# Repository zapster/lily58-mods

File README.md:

# Lily58 Mods
Modifications and enhancements for the Lily58 keyboard.

This is currently work in progress.

## Firmware
QMK with the `zapster` keymap for the Lily58 keyboard: https://github.com/zapster/qmk_firmware

## USB C Interconnect

Replace the TRRS connection with an USB C receptacle to avoid short curcuits.
The idea is to create a PCB that can be soldered to the TRRS jacks footprint.
Since the USB C is non-standard and might be confused with the USB jacks on the MCU,
the interconnect will likely use a magnetic USB C cable.

Go to [Lily58_Pro_USB_C_Reset_Ext](./Lily58_Pro_USB_C_Reset_Ext/)

### Part Evaluation:
* USB C recaptacle: USB4110-GF-A
* Magnetic USB C cable: https://www.amazon.de/gp/product/B0B76D7L5Q/ref=ppx_yo_dt_b_asin_title_o01_s00?ie=UTF8&th=1
  * need to check number of wires and connectivity

## Palm Rest

Add a palm rest and potentially 3d print a case that supports it, also wrt. tenting.

### Parts

* first try: [Kensington K52802WW](https://www.kensington.com/p/products/ergonomic-desk-accessories/ergosoft-wrist-rest/kensington-ergosoft-wrist-rest-for-standard-mouse/)
  * not comfortable
* currently testing: non-name "Powcan Memory Foam" https://www.amazon.de/gp/product/B07JGDDCJM/ref=ppx_yo_dt_b_asin_title_o00_s00?ie=UTF8&psc=1
  * until now, rather nice

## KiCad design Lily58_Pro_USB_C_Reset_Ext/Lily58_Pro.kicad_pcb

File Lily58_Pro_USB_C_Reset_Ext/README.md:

# Lily58 USB C Interconnect and Side-Reset Extension

Small extension board that adds an USB C jack for connecting the two keyboard sides
and a side-facing reset button.
The extension board is soldered onto the TRRS jack and reset button pads of the original Lily58 Pro PCB.

Similar to the main Lily58 board, the extension PCB is reversible,
so the same board can be used for the right and left side of the keyboard.

## Revision ExtUR0

The ExtUR0 revision of the PCB as been sent to the fab on 2022-11-15.

### Rendering

#### Front/Right Side

#### Back/Left Side

### Holes

| Component | Hole | Pad |
| ----------| ---- | --- |
| TRRS jack | 0.5mm x 1.6mm |1.2mm x 2.1mm|
| R1, R2, P1, P2 | 32mil (0.8128mm) | 55mil (1.3970mm) |
| Reset button | 1.3mm | 2.5mm |

### Bill of Material

For both keyboard sides.

| Qty | Part          | Description       | Comment |
| --- | ------------- | ----------------  | --- |
|   2 | TL3330AF130QG | Side-reset button | |
|   2 | USB4110-GF-A  | USB C receptacle  | |
|   8 | 3121-2-00-15-00-00-08-0 | Mill Max pin | TRRS |
|   4 | 3136-1-00-15-00-00-08-0 | Mill Max pin | Reset Button |

### Known Issues

* The part names and the board name silk screens are face the other direction. Since the parts are inherited from the Lily58 PCB, the board name should be flipped.
* All holes that connect to the Lily58 Pro PCB should probably use the same size for simplicity.

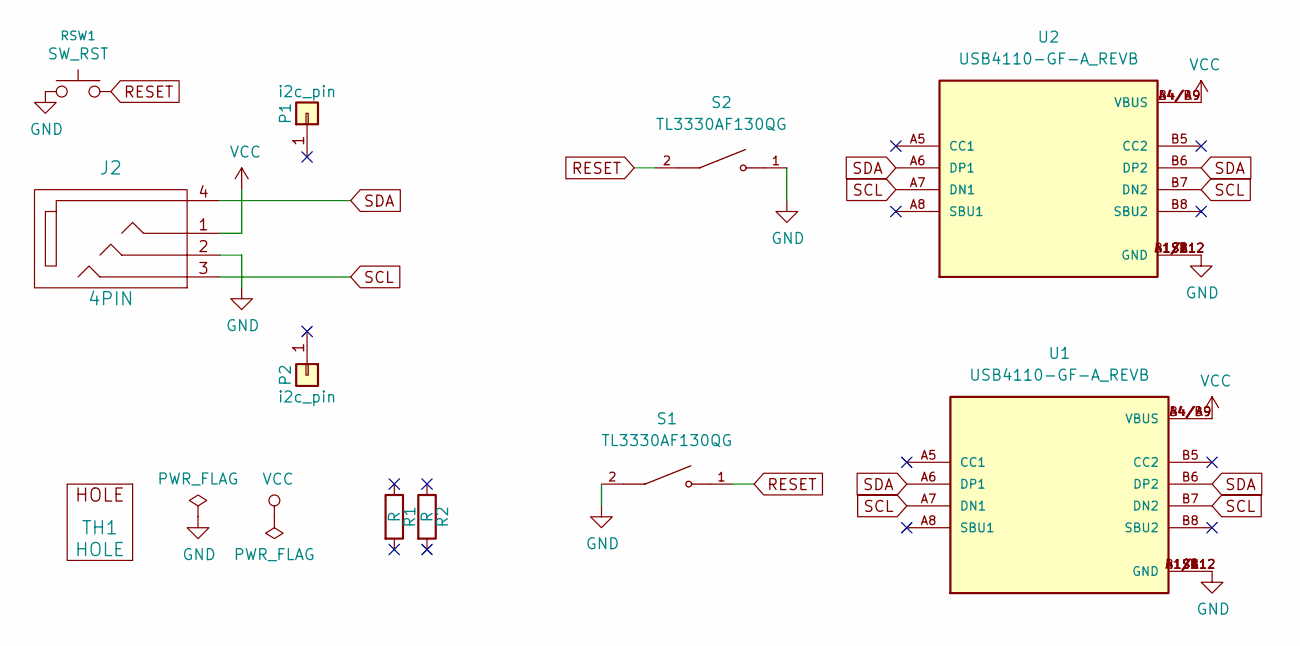
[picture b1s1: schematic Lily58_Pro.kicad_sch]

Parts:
J2: 4PIN; MJ-4PP-9
P1, P2: i2c_pin; 1pin_conn
R1, R2: R; RESISTOR_mini
RSW1: SW_RST; TACT_SWITCH_TVBP06
S1, S2: TL3330AF130QG; SW_TL3330AF130QG; PARTREV B
TH1: HOLE; M2_HOLE_PCB
U1, U2: USB4110-GF-A_REVB; GCT_USB4110-GF-A_REVB; PARTREV B

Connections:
GND: J2.2, RSW1.1, S1.2, S2.1, U1.A1/B12 (GND), U1.B1/A12 (GND), U1.S1 (GND), U1.S2 (GND), U1.S3 (GND), U1.S4 (GND), U2.A1/B12 (GND), U2.B1/A12 (GND), U2.S1 (GND), U2.S2 (GND), U2.S3 (GND), U2.S4 (GND)
RESET: RSW1.2, S1.1, S2.2
SCL: J2.3, U1.A7 (DN1), U1.B7 (DN2), U2.A7 (DN1), U2.B7 (DN2)
SDA: J2.4, U1.A6 (DP1), U1.B6 (DP2), U2.A6 (DP1), U2.B6 (DP2)
VCC: J2.1, U1.A4/B9 (VBUS), U1.B4/A9 (VBUS), U2.A4/B9 (VBUS), U2.B4/A9 (VBUS)

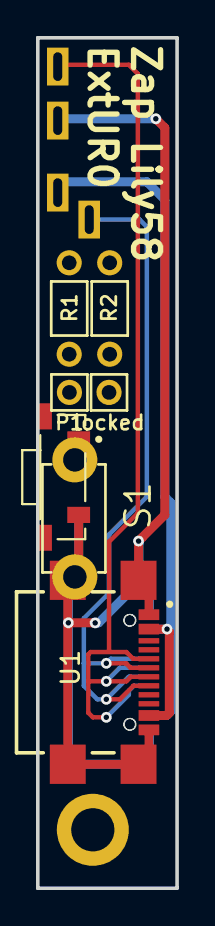
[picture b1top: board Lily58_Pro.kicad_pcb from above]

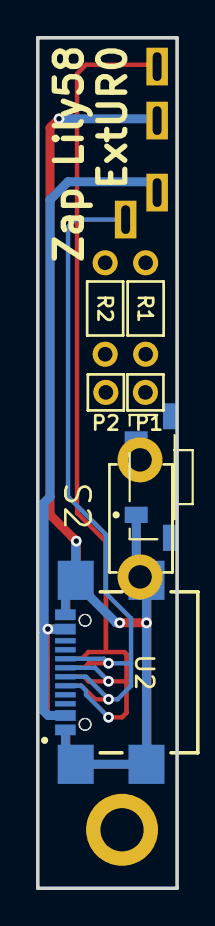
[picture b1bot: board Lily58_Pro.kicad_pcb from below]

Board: 2 copper layers, 7.7 x 47.2 mm, 11 parts (2 on the bottom side), 5 nets.

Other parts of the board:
locked: i2c_pin; 1pin_conn

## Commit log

2022-11-12 Lily58_mod_trrs: add initial back version
2022-11-12 Lily58_Pro_USB_C_Reset_Ext: drop Lily58 Pro files
2022-11-12 Lily58_Pro_USB_C_Reset_Ext: convert to new KiCad format
2022-11-12 Lily58_Pro_USB_C_Reset_Ext: remove old files
2022-11-12 Lily58_Pro_USB_C_Reset_Ext: strip down
2022-11-12 Lily58_Pro_USB_C_Reset_Ext: add usb and reset
2022-11-13 Lily58_Pro_USB_C_Reset_Ext: change trrs jack and replace usb to metric
2022-11-14 Lily58_Pro_USB_C_Reset_Ext: routing
2022-11-14 Lily58_Pro_USB_C_Reset_Ext: better routing
2022-11-15 Lily58_Pro_USB_C_Reset_Ext: remove fill
2022-11-15 Lily58_Pro_USB_C_Reset_Ext: update via size
2022-11-16 Lily58_Pro_USB_C_Reset_Ext: add docs
2022-11-16 Lily58_Pro_USB_C_Reset_Ext: add known issues
2022-11-16 Lily58_Pro_USB_C_Reset_Ext: add hole doc
2022-11-16 Lily58_Pro_USB_C_Reset_Ext: Pins
2022-11-17 Lily58_Pro_USB_C_Reset_Ext: fix BOM quantities
2022-11-17 Lily58_Pro_USB_C_Reset_Ext: minor
2022-11-26 Lily58_Pro_case: initial
2022-11-29 Lily58_Pro_bento_travel_case: copy
2022-11-29 Lily58_Pro_bento_travel_case: add sketches and spreadsheet
2022-11-29 Lily58_Pro_bento_travel_case: extrude case
2022-11-30 Lily58_Pro_bento_travel_case: base case ready
2022-11-30 Lily58_Pro_bento_travel_case: right dimensions
2022-11-30 Lily58_Pro_bento_travel_case: v1 draft
2022-12-01 Lily58_Pro_bento_travel_case: add readme
2022-12-29 Lily58_Pro_bento_travel_case: deeper cut-out
2022-12-29 Lily58_Pro_bento_travel_case: reduce keyspace to 15mm
2022-12-29 Lily58_Pro_bento_travel_case: add version number
2023-03-12 BentoTravelCase: left side
2023-03-12 BentoTravelCase: mirrored
2023-03-12 BentoTravelCase: v1 with logo
2024-01-08 Lily58_extra_thumb_switch_mod: init
2024-01-08 Lily58_extra_thumb_switch_mod: bigger bottom
2024-01-08 Lily58_extra_thumb_switch_mod: v3
2024-01-10 Lily58_extra_thumb_switch_mod: case init
2024-01-10 Lily58_extra_thumb_switch_mod: clean up
2024-01-10 Lily58_extra_thumb_switch_mod: keyboard approximation
2024-01-11 Lily58_extra_thumb_switch_mod: redraw
2024-01-11 Lily58_extra_thumb_switch_mod: placement
2024-01-11 Lily58_extra_thumb_switch_mod: rev1
2024-01-27 CaseInlay: draw
2024-01-27 CaseInlay: sections
2025-05-06 Lily58_extra_thumb_switch_mod: case inlay svgs
